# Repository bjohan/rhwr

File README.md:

# rhwr
backend and support system for rhwr from tornado aircraft. mostly a mess...

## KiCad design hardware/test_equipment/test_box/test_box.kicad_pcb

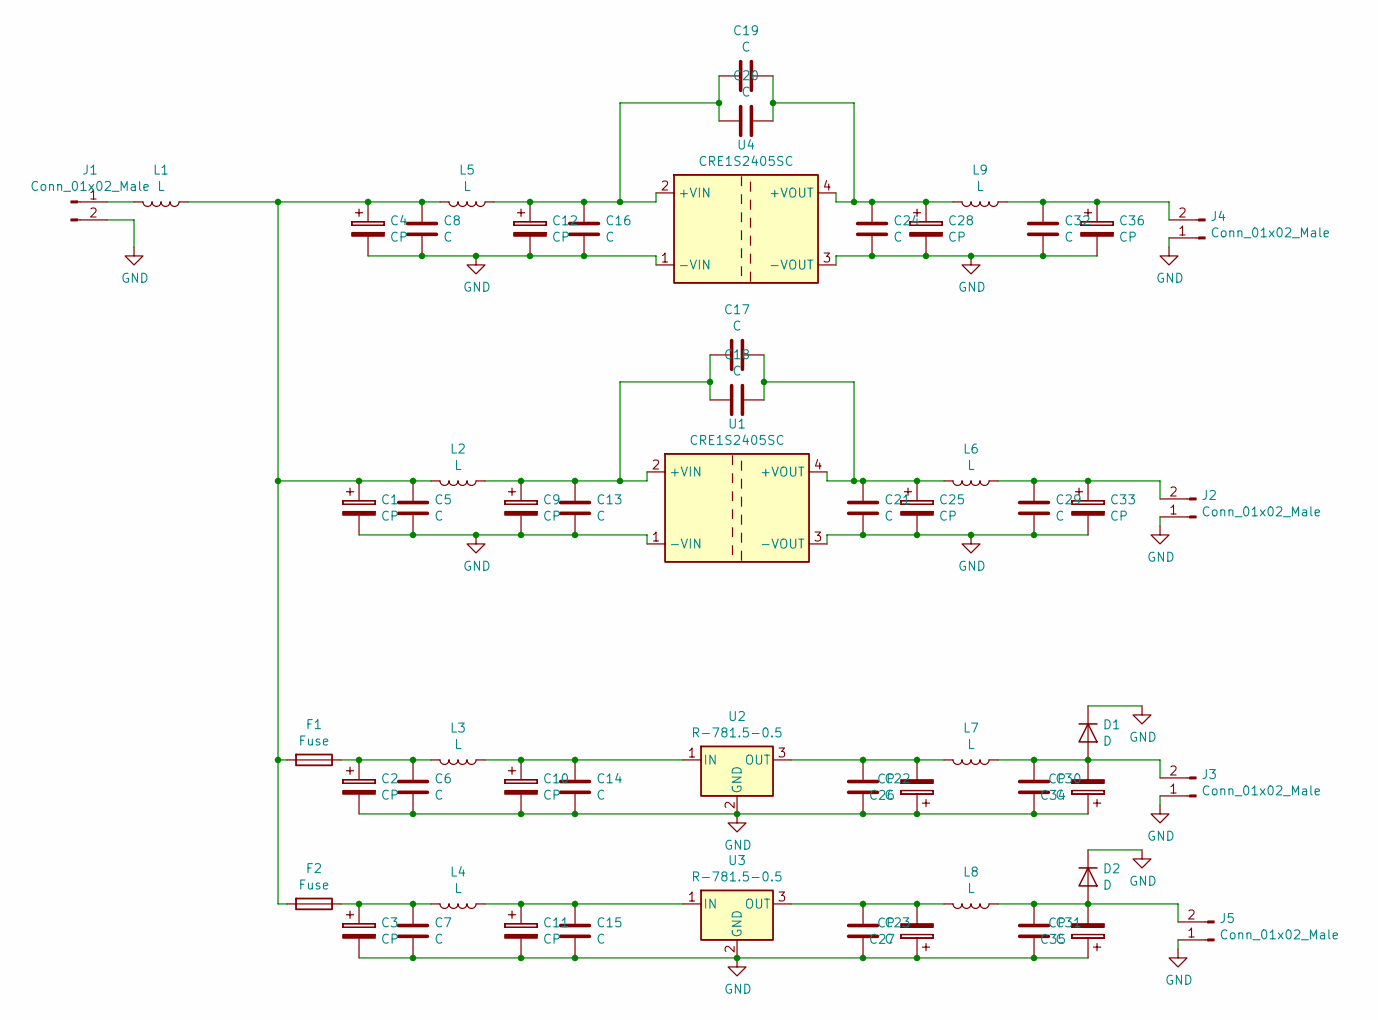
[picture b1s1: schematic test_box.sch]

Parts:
C1, C2, C3, C4, C9, C10, C11, C12, C25, C26, C27, C28, C33, C34, C35, C36: CP; CP_Elec_10x10.5
C5, C6, C7, C8, C13, C14, C15, C16, C17, C18, C19, C20, C21, C22, C23, C24, C29, C30, C31, C32: C; C_1206
D1, D2: D; D_2010
F1, F2: Fuse; R_1206
J1, J2, J3, J4, J5: Conn_01x02_Male; Molex_KK-6410-02_02x2.54mm_Straight
L1, L2, L3, L4, L5, L6, L7, L8, L9: L; Neosid_Inductor_SM-NE127
U1: CRE1S2405SC; 2149f
U2, U3: R-781.5-0.5; 0663ac
U4: CRE1S2405SC; cn6009psu

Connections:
GND: C1.2, C2.2, C3.2, C4.2, C5.2, C6.2, C7.2, C8.2, C9.2, C10.2, C11.2, C12.2, C13.2, C14.2, C15.2, C16.2, C21.2, C22.2, C23.2, C24.2, C25.2, C26.1, C27.1, C28.2, C29.2, C30.2, C31.2, C32.2, C33.2, C34.1, C35.1, C36.2, D1.1 (K), D2.1 (K), J1.2, J2.1, J3.1, J4.1, J5.1, U1.1 (-VIN), U1.3 (-VOUT), U2.2 (GND), U3.2 (GND), U4.1 (-VIN), U4.3 (-VOUT)
unnamed: C1.1, C4.1, C5.1, C8.1, F1.2, F2.2, L1.1, L2.2, L5.2
unnamed: C2.1, C6.1, F1.1, L3.2
unnamed: C3.1, C7.1, F2.1, L4.2
unnamed: C10.1, C14.1, L3.1, U2.1 (IN)
unnamed: C11.1, C15.1, L4.1, U3.1 (IN)
unnamed: C12.1, C16.1, C19.2, C20.2, L5.1, U4.2 (+VIN)
unnamed: C9.1, C13.1, C17.2, C18.2, L2.1, U1.2 (+VIN)
unnamed: C17.1, C18.1, C21.1, C25.1, L6.2, U1.4 (+VOUT)
unnamed: C19.1, C20.1, C24.1, C28.1, L9.2, U4.4 (+VOUT)
unnamed: C22.1, C26.2, L7.2, U2.3 (OUT)
unnamed: C23.1, C27.2, L8.2, U3.3 (OUT)
unnamed: C29.1, C33.1, J2.2, L6.1
unnamed: C30.1, C34.2, D1.2 (A), J3.2, L7.1
unnamed: C31.1, C35.2, D2.2 (A), J5.2, L8.1
unnamed: C32.1, C36.1, J4.2, L9.1
unnamed: J1.1, L1.2

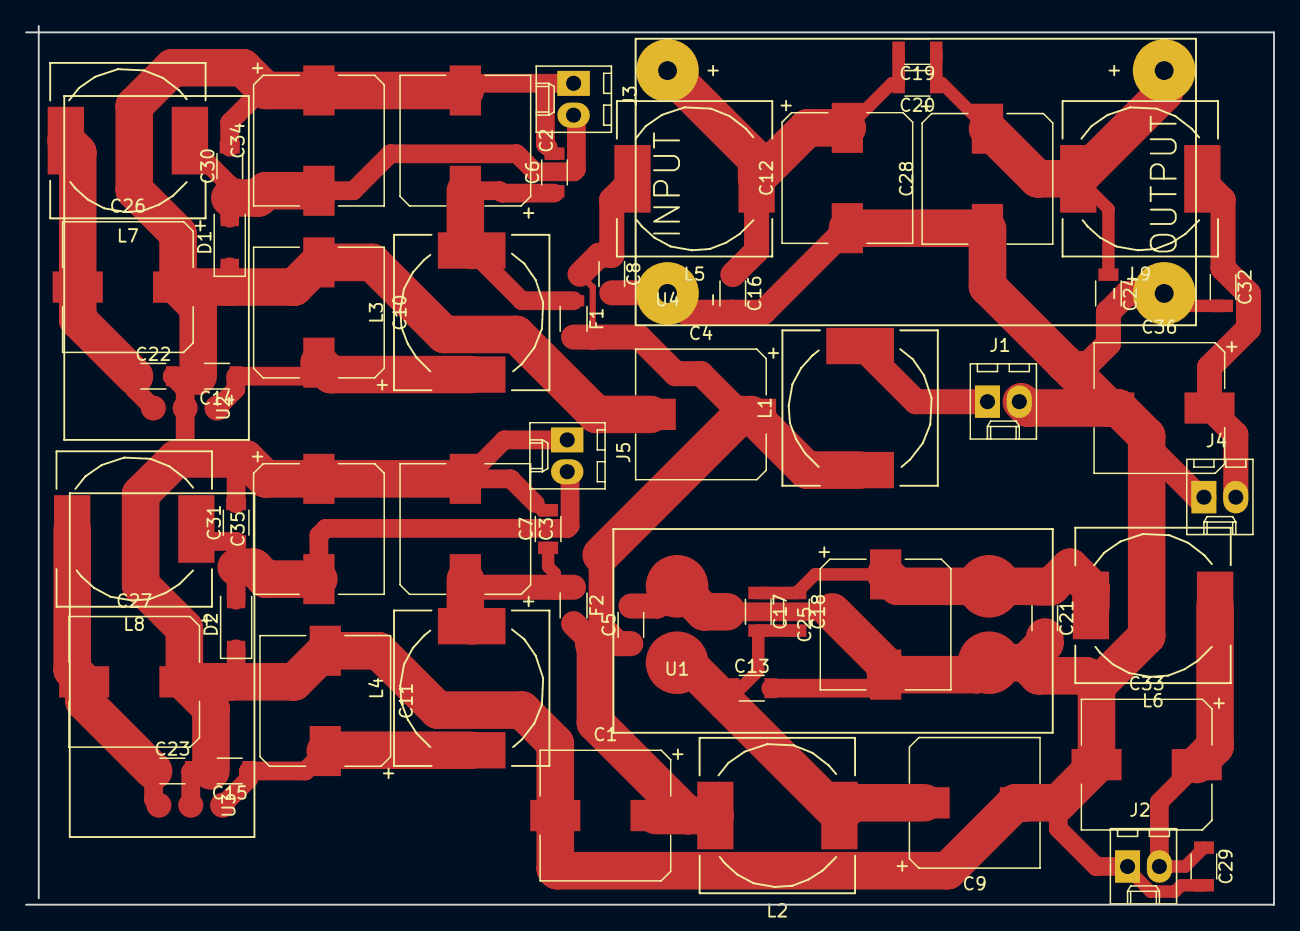
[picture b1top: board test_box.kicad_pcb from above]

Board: 2 copper layers, 99.6 x 70.1 mm, 58 parts (0 on the bottom side), 17 nets.

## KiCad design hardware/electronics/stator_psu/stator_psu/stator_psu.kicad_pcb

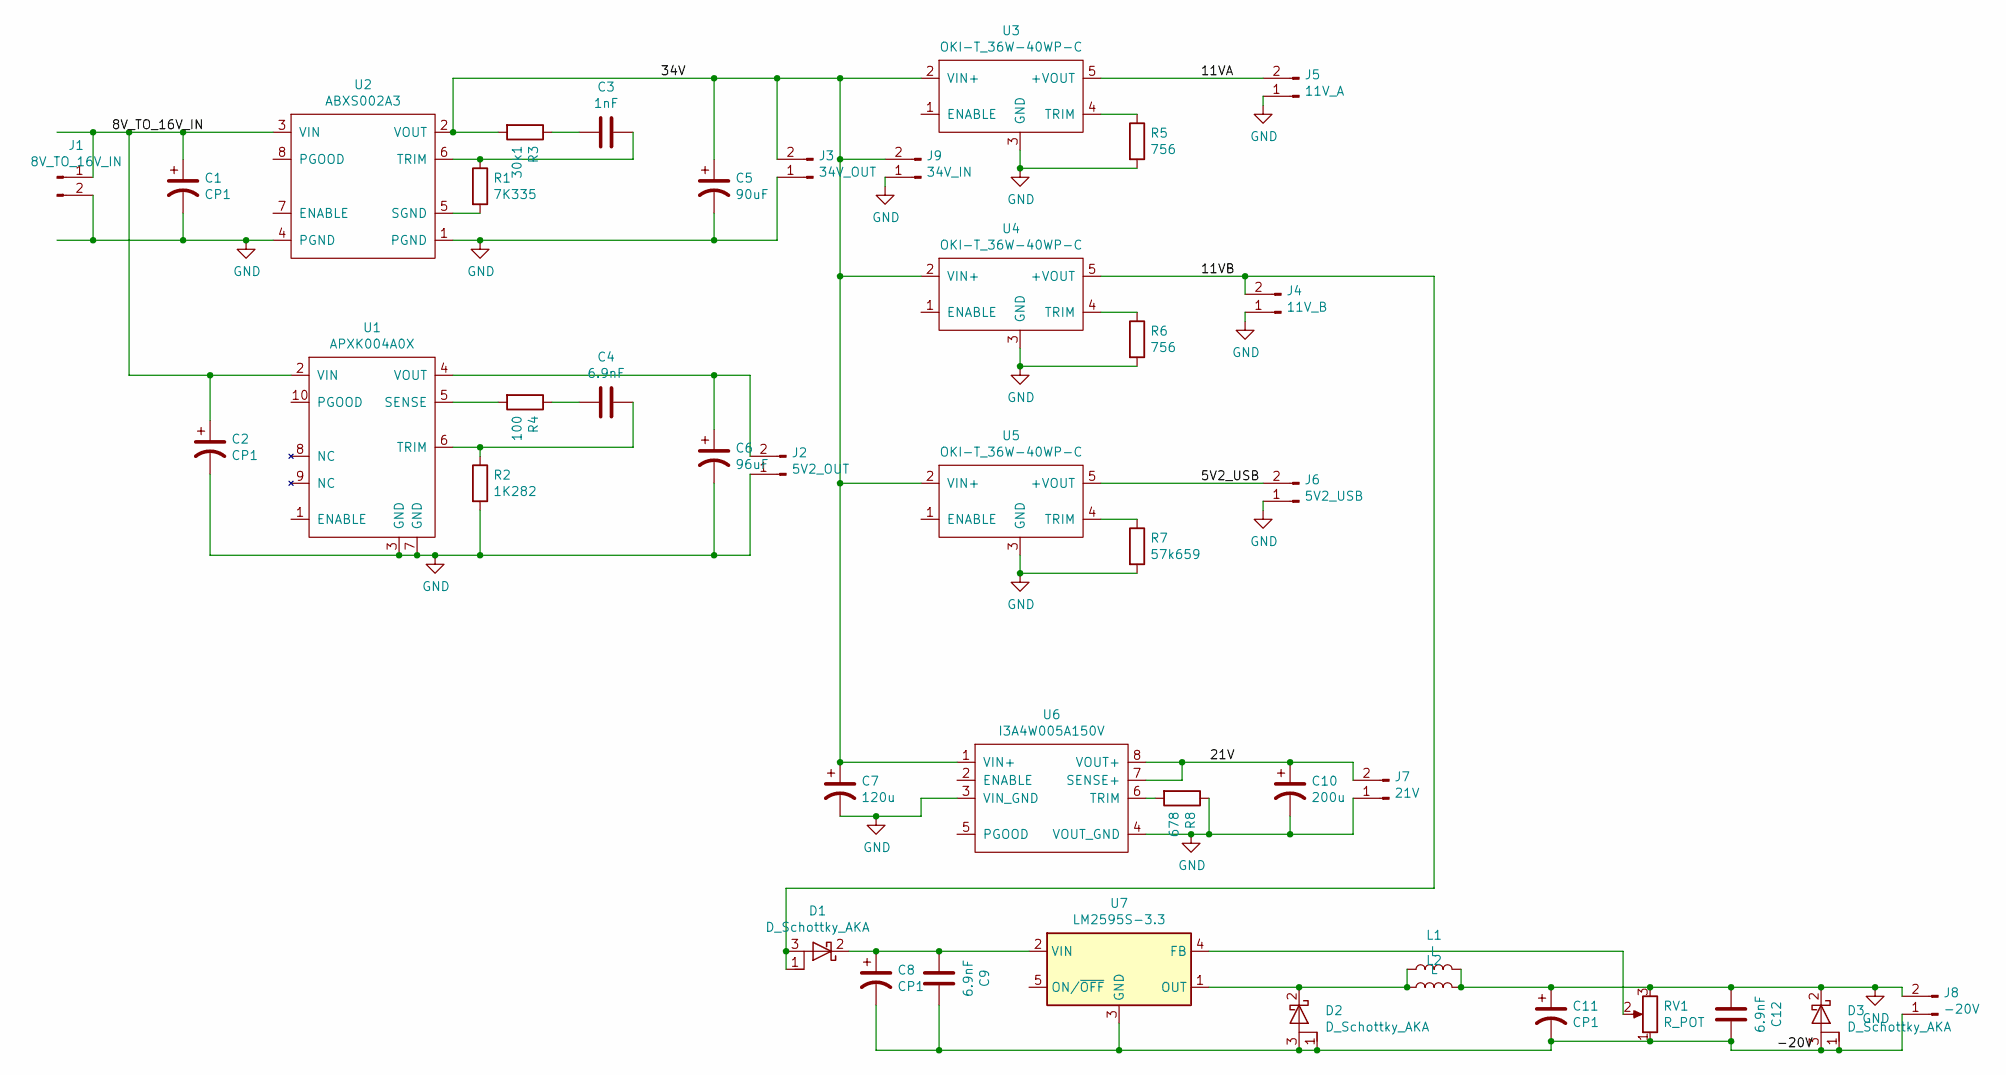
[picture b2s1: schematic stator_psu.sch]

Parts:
C1, C2, C8, C11: CP1; CP_Elec_10x10.5
C3: 1nF; C_1206
C4, C9, C12: 6.9nF; C_1206
C5: 90uF; CP_Elec_10x10.5
C6: 96uF; CP_Elec_10x10.5
C7: 120u; CP_Elec_10x10.5
C10: 200u; CP_Elec_10x10.5
D1, D2, D3: D_Schottky_AKA; TO-220
J1: 8V_TO_16V_IN; PhoenixContact_MSTBA-G_02x5.08mm_Angled
J2: 5V2_OUT; PhoenixContact_MSTBA-G_02x5.08mm_Angled
J3: 34V_OUT; PhoenixContact_MSTBA-G_02x5.08mm_Angled
J4: 11V_B; Molex_SPOX-5267_22-03-5025_02x2.54mm_Straight
J5: 11V_A; Molex_SPOX-5267_22-03-5025_02x2.54mm_Straight
J6: 5V2_USB; PhoenixContact_MSTBA-G_02x5.08mm_Angled
J7: 21V; Molex_SPOX-5267_22-03-5025_02x2.54mm_Straight
J8: -20V; Molex_SPOX-5267_22-03-5025_02x2.54mm_Straight
J9: 34V_IN; PhoenixContact_MSTBA-G_02x5.08mm_Angled
L1, L2: L; Neosid_Inductor_Ms95
R1: 7K335; R_1206
R2: 1K282; R_1206
R3: 30k1; R_1206
R4: 100; R_1206
R5, R6: 756; R_1206
R7: 57k659; R_1206
R8: 678; R_1206
RV1: R_POT; POT_SMD
U1: APXK004A0X
U2: ABXS002A3
U3, U4, U5: OKI-T_36W-40WP-C; OKI-T_36W-w40
U6: I3A4W005A150V; I3A4W005A150
U7: LM2595S-3.3; TO-263-5_TabPin3

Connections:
/5V2_USB: J6.2, U5.5 (+VOUT)
/8V_TO_16V_IN: C1.1, C2.1, J1.1, U1.2 (VIN), U2.3 (VIN)
/11VA: J5.2, U3.5 (+VOUT)
/11VB: D1.1 (A), D1.3 (A), J4.2, U4.5 (+VOUT)
/21V: C10.1, J7.2, U6.7 (SENSE+), U6.8 (VOUT+)
/34V: C5.1, C7.1, J3.2, J9.2, R3.2, U2.2 (VOUT), U3.2 (VIN+), U4.2 (VIN+), U5.2 (VIN+), U6.1 (VIN+)
/-20V: C8.2, C9.1, C11.2, C12.1, D2.1 (A), D2.3 (A), D3.1 (A), D3.3 (A), J8.1, RV1.1, U7.3 (GND)
GND: C1.2, C2.2, C5.2, C6.2, C7.2, C10.2, C11.1, C12.2, D3.2 (K), J1.2, J2.1, J3.1, J4.1, J5.1, J6.1, J7.1, J8.2, J9.1, L1.2, L2.2, R2.2, R5.2, R6.2, R7.2, R8.1, RV1.3, U1.3 (GND), U1.7 (GND), U2.1 (PGND), U2.4 (PGND), U3.3 (GND), U4.3 (GND), U5.3 (GND), U6.3 (VIN_GND), U6.4 (VOUT_GND)
unnamed: C3.1, R1.1, U2.6 (TRIM)
unnamed: C3.2, R3.1
unnamed: C4.1, R2.1, U1.6 (TRIM)
unnamed: C4.2, R4.1
unnamed: C6.1, J2.2, U1.4 (VOUT)
unnamed: C8.1, C9.2, D1.2 (K), U7.2 (VIN)
unnamed: D2.2 (K), L1.1, L2.1, U7.1 (OUT)
unnamed: R1.2, U2.5 (SGND)
unnamed: R4.2, U1.5 (SENSE)
unnamed: R5.1, U3.4 (TRIM)
unnamed: R6.1, U4.4 (TRIM)
unnamed: R7.1, U5.4 (TRIM)
unnamed: R8.2, U6.6 (TRIM)
unnamed: RV1.2, U7.4 (FB)

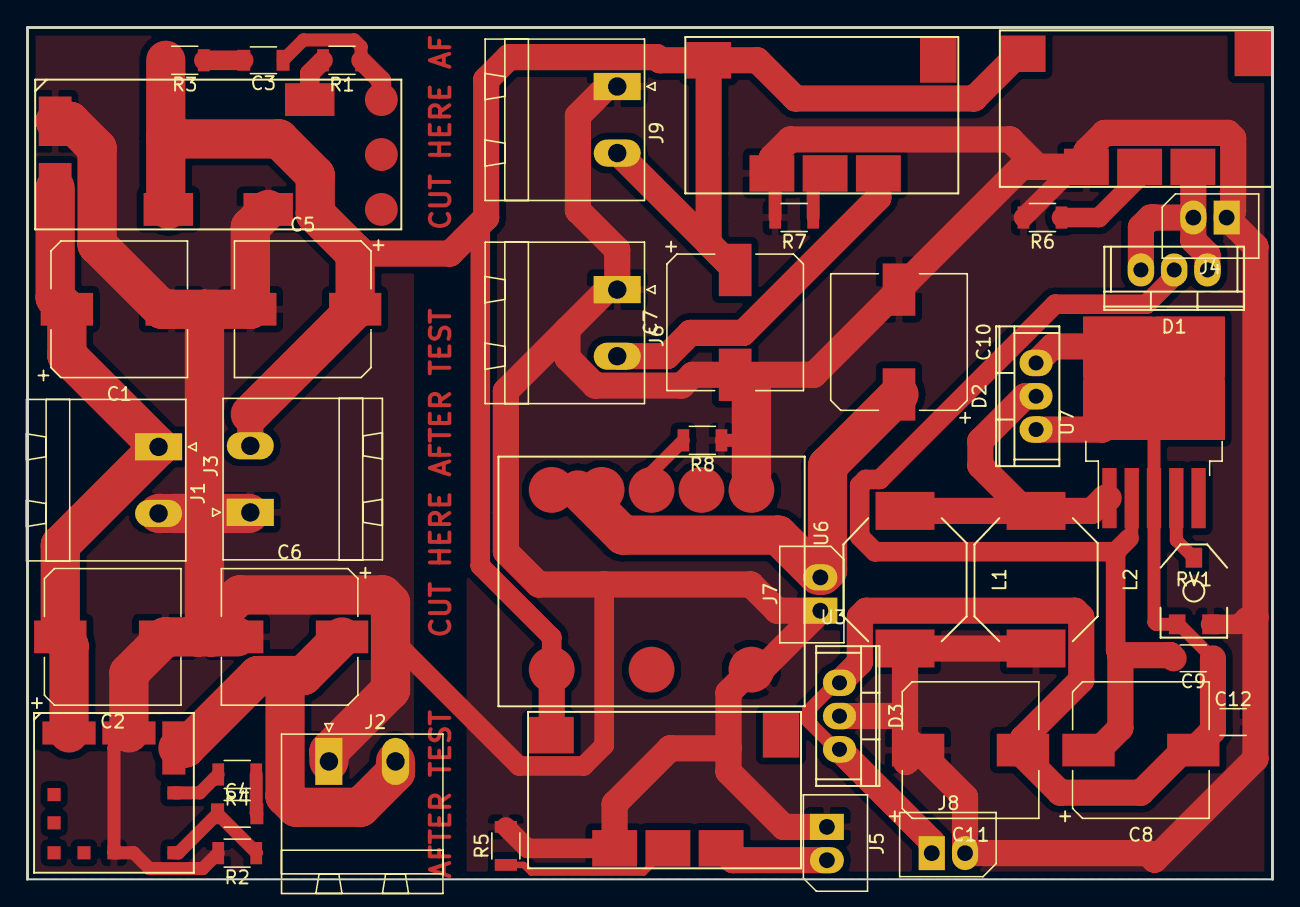
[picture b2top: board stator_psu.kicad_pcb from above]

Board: 2 copper layers, 95.0 x 65.0 mm, 42 parts (0 on the bottom side), 22 nets.

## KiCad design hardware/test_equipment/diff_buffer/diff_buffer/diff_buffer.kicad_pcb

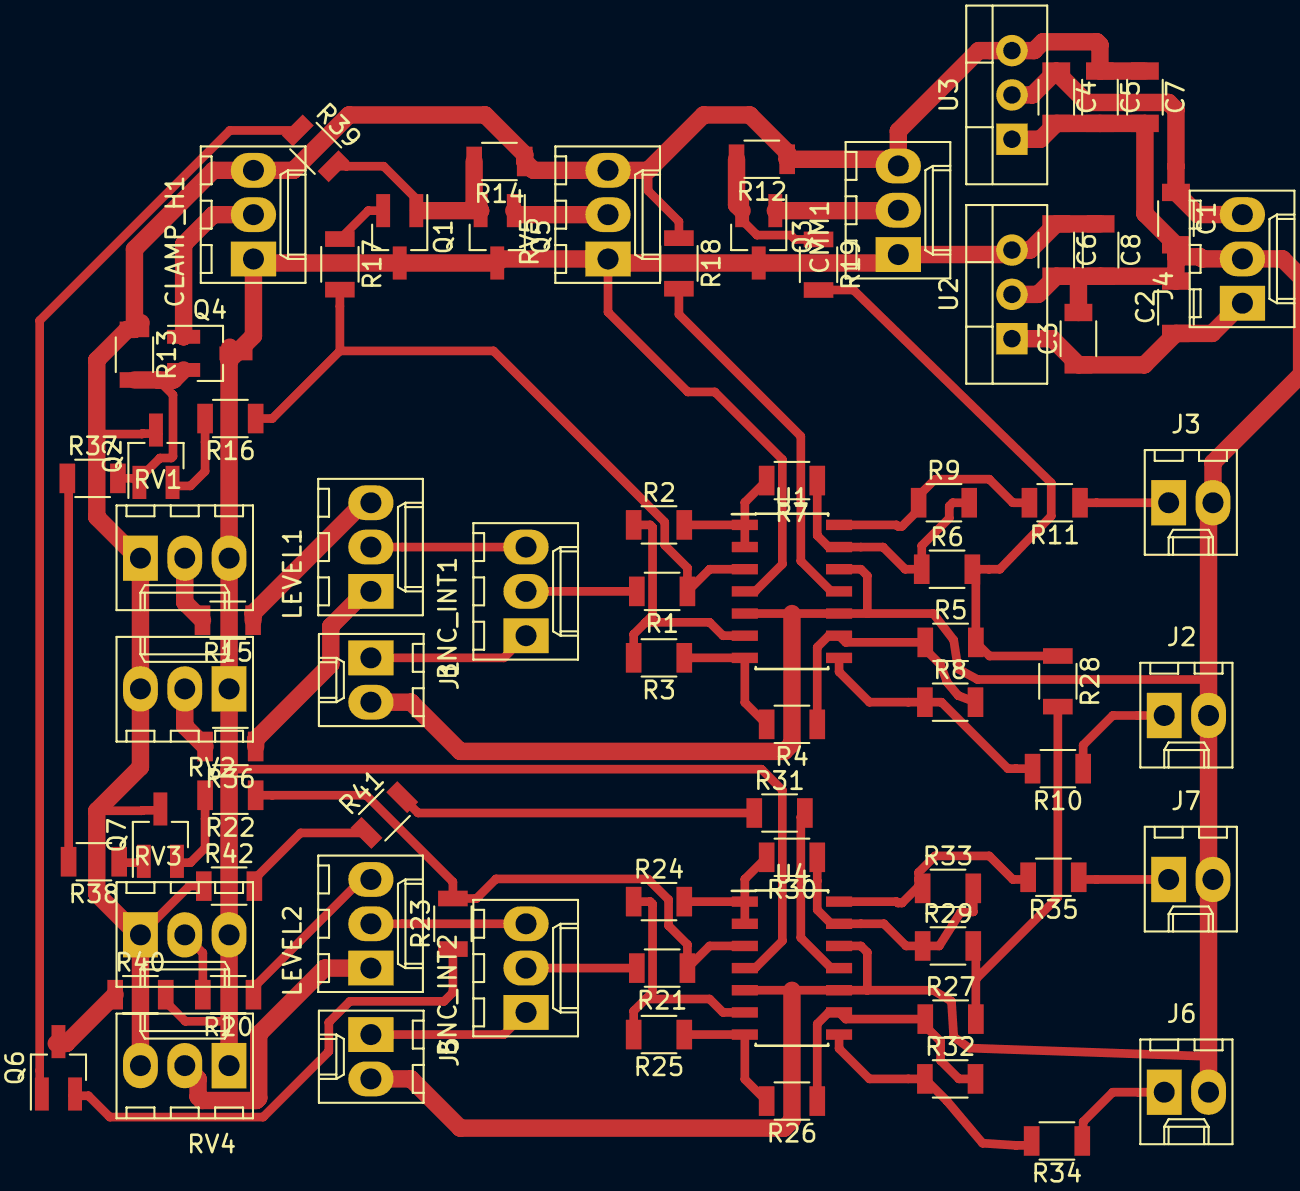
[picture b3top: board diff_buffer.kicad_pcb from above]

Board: 2 copper layers, 79 parts (0 on the bottom side), 58 nets.

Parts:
BNC_INT1, BNC_INT2: SW_SPDT; Molex_KK-6410-03_03x2.54mm_Straight
C1, C2, C3, C4, C5, C6, C7, C8: C; C_1206
CLAMP_H1: R_POT; Molex_KK-6410-03_03x2.54mm_Straight
CMM1: R_POT; Molex_KK-6410-03_03x2.54mm_Straight
J1, J5: INPUT; Molex_KK-6410-02_02x2.54mm_Straight
J2, J6: ~OUT; Molex_KK-6410-02_02x2.54mm_Straight
J3, J7: OUT; Molex_KK-6410-02_02x2.54mm_Straight
J4: Conn_01x03_Male; Molex_KK-6410-03_03x2.54mm_Straight
LEVEL1, LEVEL2: SW_SPDT; Molex_KK-6410-03_03x2.54mm_Straight
Q1, Q6: Q_NPN_BEC; SOT-23_Handsoldering
Q2, Q3, Q4, Q5, Q7: Q_PNP_BEC; SOT-23_Handsoldering
R1, R2, R3, R4, R5, R6, R7, R8, R9, R21, R24, R25, R26, R27, R29, R30, R32, R33: 100K; R_1206
R10, R11, R34, R35: 10K; R_1206
R12, R13, R14, R18, R39: R; R_1206
R15, R19, R20, R28, R31, R36, R37, R38, R40, R41, R42: 0; R_1206
R16, R17, R22, R23: 2K; R_1206
RV1, RV2, RV3, RV4: R_POT; Molex_KK-6410-03_03x2.54mm_Straight
RV5: CLAMP_L; Molex_KK-6410-03_03x2.54mm_Straight
U1, U4: LM324; SOIC-14_3.9x8.7mm_Pitch1.27mm
U2: L7812; TO-220-3_Vertical
U3: L7912; TO-220-3_Vertical

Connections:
+15V: C6.1, C8.1, CLAMP_H1.1, CMM1.1, Q1.3, Q3.3, Q4.3, Q5.3, R40.2, RV1.3, RV2.1, RV3.3, RV4.1, RV5.1, U1.4, U2.3, U4.4
-15V: C5.1, C7.1, CLAMP_H1.3, CMM1.3, Q2.3, Q7.3, R12.1, R13.1, R14.1, R18.1, R42.1, RV1.1, RV2.3, RV3.1, RV4.3, RV5.3, U3.3
/neg_clamp_voltage: Q1.1, Q5.2, R14.2, R39.2
/offset_voltage: Q3.2, R12.2, R19.1
/offset_voltage2: R5.2, R6.2, R19.2, R28.1
/pos_clamp_voltage: Q2.1, Q4.2, R13.2, R37.2
GND: C1.2, C2.2, C3.2, C4.2, C5.2, C6.2, C7.2, C8.2, J1.2, J2.2, J3.2, J4.2, J5.2, J6.2, J7.2, U1.5, U1.10, U1.12, U2.2, U3.1, U4.5, U4.10, U4.12
unnamed: BNC_INT1.1, J1.1
unnamed: BNC_INT1.2, R1.2
unnamed: BNC_INT1.3, LEVEL1.2
unnamed: BNC_INT2.1, J5.1
unnamed: BNC_INT2.2, R21.2
unnamed: BNC_INT2.3, LEVEL2.2
unnamed: C1.1, C4.1, J4.3, U3.2
unnamed: C2.1, C3.1, J4.1, U2.1
unnamed: CLAMP_H1.2, Q4.1
unnamed: CMM1.2, Q3.1
unnamed: J2.1, R10.1
unnamed: J3.1, R11.1
unnamed: J6.1, R34.1
unnamed: J7.1, R35.1
unnamed: LEVEL1.1, R36.1
unnamed: LEVEL1.3, R15.1
unnamed: LEVEL2.1, RV4.2
unnamed: LEVEL2.3, R20.1
unnamed: Q1.2, R17.1
unnamed: Q2.2, R16.2
unnamed: Q5.1, RV5.2
unnamed: Q6.1, R39.1
unnamed: Q6.2, R23.1
unnamed: Q6.3, R40.1
unnamed: Q7.1, R38.1
unnamed: Q7.2, R22.2
unnamed: R1.1, R16.1, R17.2, U1.3
unnamed: R2.1, R3.2, U1.6
unnamed: R2.2, R7.2, U1.1, U1.2
unnamed: R3.1, R4.2, U1.7
unnamed: R4.1, R5.1, R8.2, U1.9
unnamed: R6.1, R7.1, R9.2, U1.13
unnamed: R8.1, R10.2, U1.8
unnamed: R9.1, R11.2, U1.14
unnamed: R15.2, RV1.2
unnamed: R18.2, U1.11
unnamed: R20.2, RV3.2
unnamed: R21.1, R22.1, R23.2, U4.3
unnamed: R24.1, R25.2, U4.6
unnamed: R24.2, R30.2, U4.1, U4.2
unnamed: R25.1, R26.2, U4.7
unnamed: R26.1, R27.1, R32.2, U4.9
unnamed: R27.2, R28.2, R29.2
unnamed: R29.1, R30.1, R33.2, U4.13
unnamed: R31.1, R41.2
unnamed: R31.2, U4.11
unnamed: R32.1, R34.2, U4.8
unnamed: R33.1, R35.2, U4.14
unnamed: R36.2, RV2.2
unnamed: R37.1, R38.2
unnamed: R41.1, R42.2

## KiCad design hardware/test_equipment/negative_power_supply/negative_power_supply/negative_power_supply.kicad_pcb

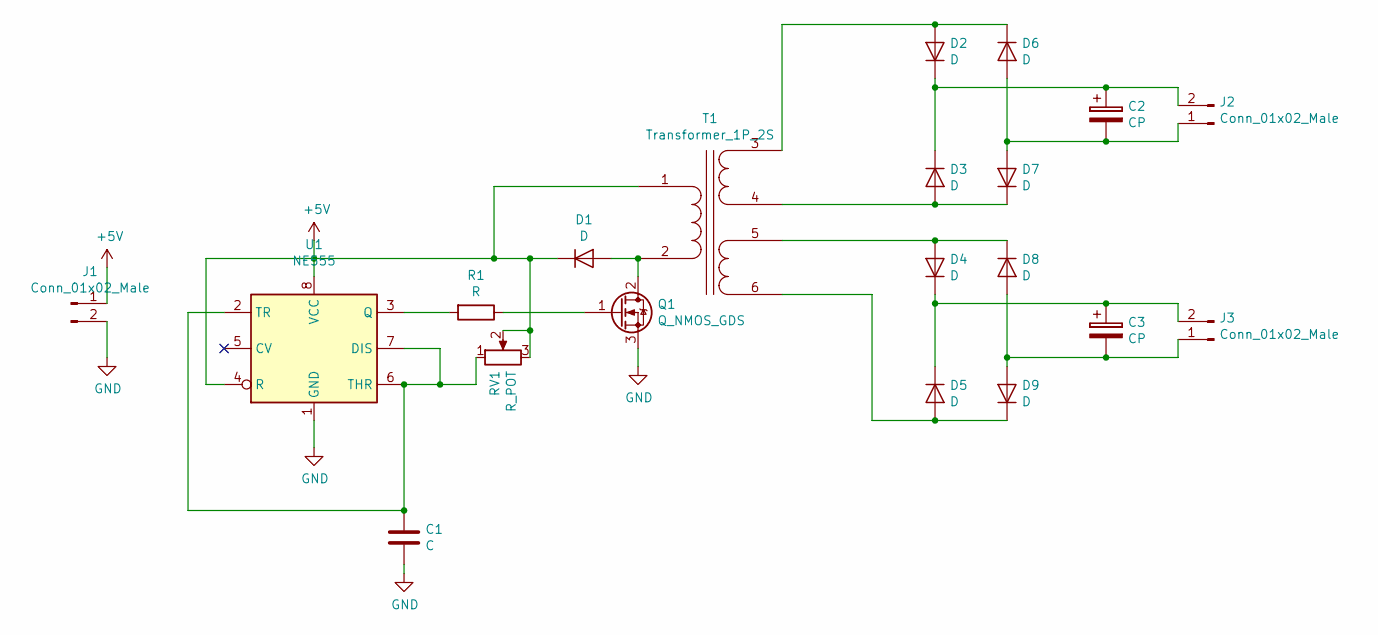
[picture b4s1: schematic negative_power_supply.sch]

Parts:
C1: C; C_1206
C2, C3: CP; CP_Elec_10x10.5
D1, D2, D3, D4, D5, D6, D7, D8, D9: D; D_SMA_Handsoldering
J1, J2, J3: Conn_01x02_Male; Molex_KK-6410-02_02x2.54mm_Straight
Q1: Q_NMOS_GDS; TO-220
R1: R; R_1206
RV1: R_POT; Potentiometer_Trimmer_ACP_CA6VSMD_Horizontal
T1: Transformer_1P_2S; Molex_KK-6410-06_06x2.54mm_Straight
U1: NE555; DIP-8_W7.62mm_LongPads

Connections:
+5V: D1.1 (K), J1.1, RV1.2, RV1.3, T1.1 (AA), U1.4 (R), U1.8 (VCC)
GND: C1.2, J1.2, Q1.3 (S), U1.1 (GND)
unnamed: C1.1, RV1.1, U1.2 (TR), U1.6 (THR), U1.7 (DIS)
unnamed: C2.1, D2.1 (K), D3.1 (K), J2.2
unnamed: C2.2, D6.2 (A), D7.2 (A), J2.1
unnamed: C3.1, D4.1 (K), D5.1 (K), J3.2
unnamed: C3.2, D8.2 (A), D9.2 (A), J3.1
unnamed: D1.2 (A), Q1.2 (D), T1.2 (AB)
unnamed: D2.2 (A), D6.1 (K), T1.3 (SA)
unnamed: D3.2 (A), D7.1 (K), T1.4 (SB)
unnamed: D4.2 (A), D8.1 (K), T1.5 (SC)
unnamed: D5.2 (A), D9.1 (K), T1.6 (SD)
unnamed: Q1.1 (G), R1.1
unnamed: R1.2, U1.3 (Q)

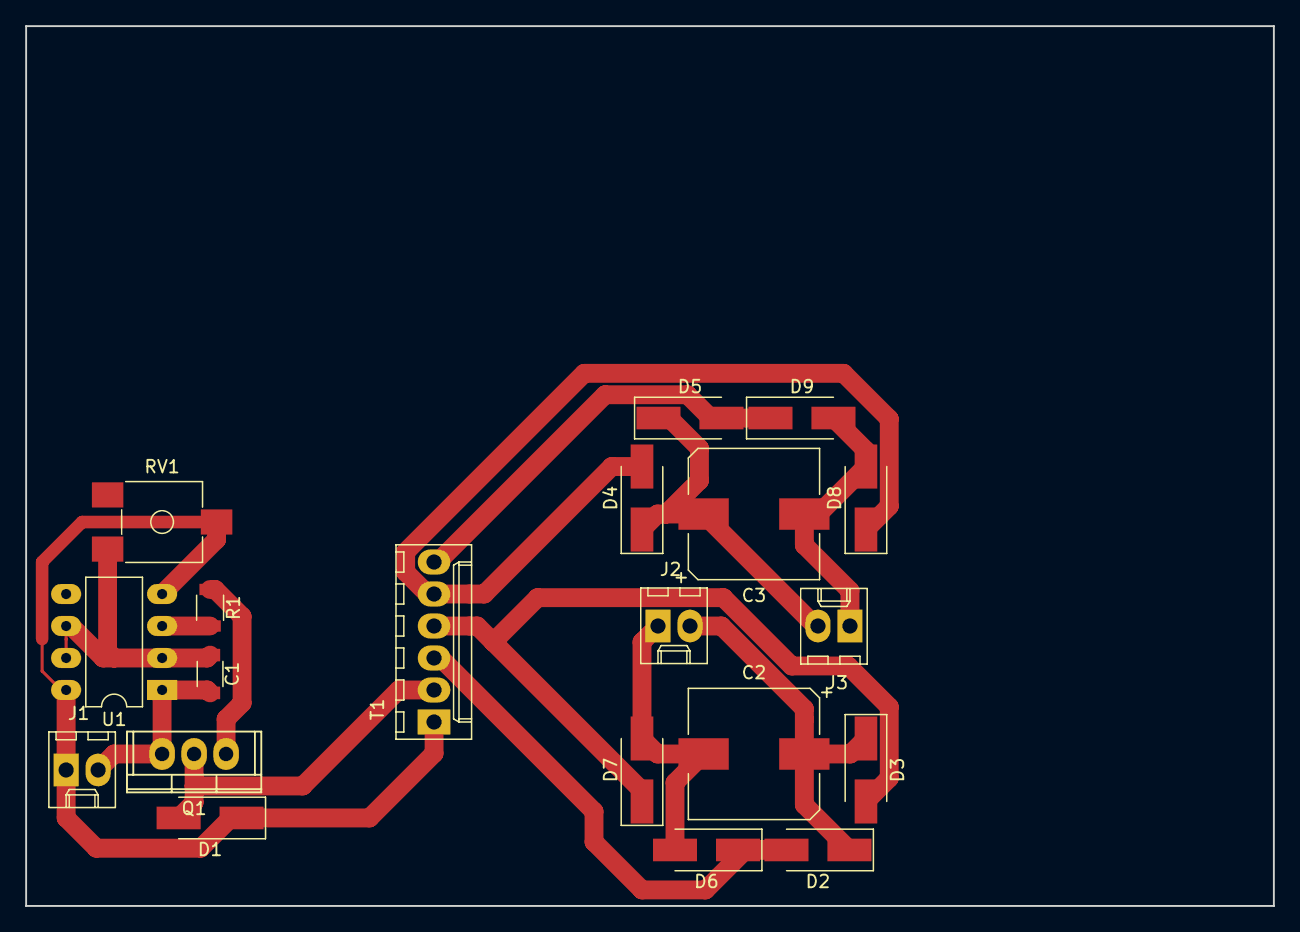
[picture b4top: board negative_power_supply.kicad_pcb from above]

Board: 2 copper layers, 99.1 x 69.9 mm, 20 parts (0 on the bottom side), 14 nets.

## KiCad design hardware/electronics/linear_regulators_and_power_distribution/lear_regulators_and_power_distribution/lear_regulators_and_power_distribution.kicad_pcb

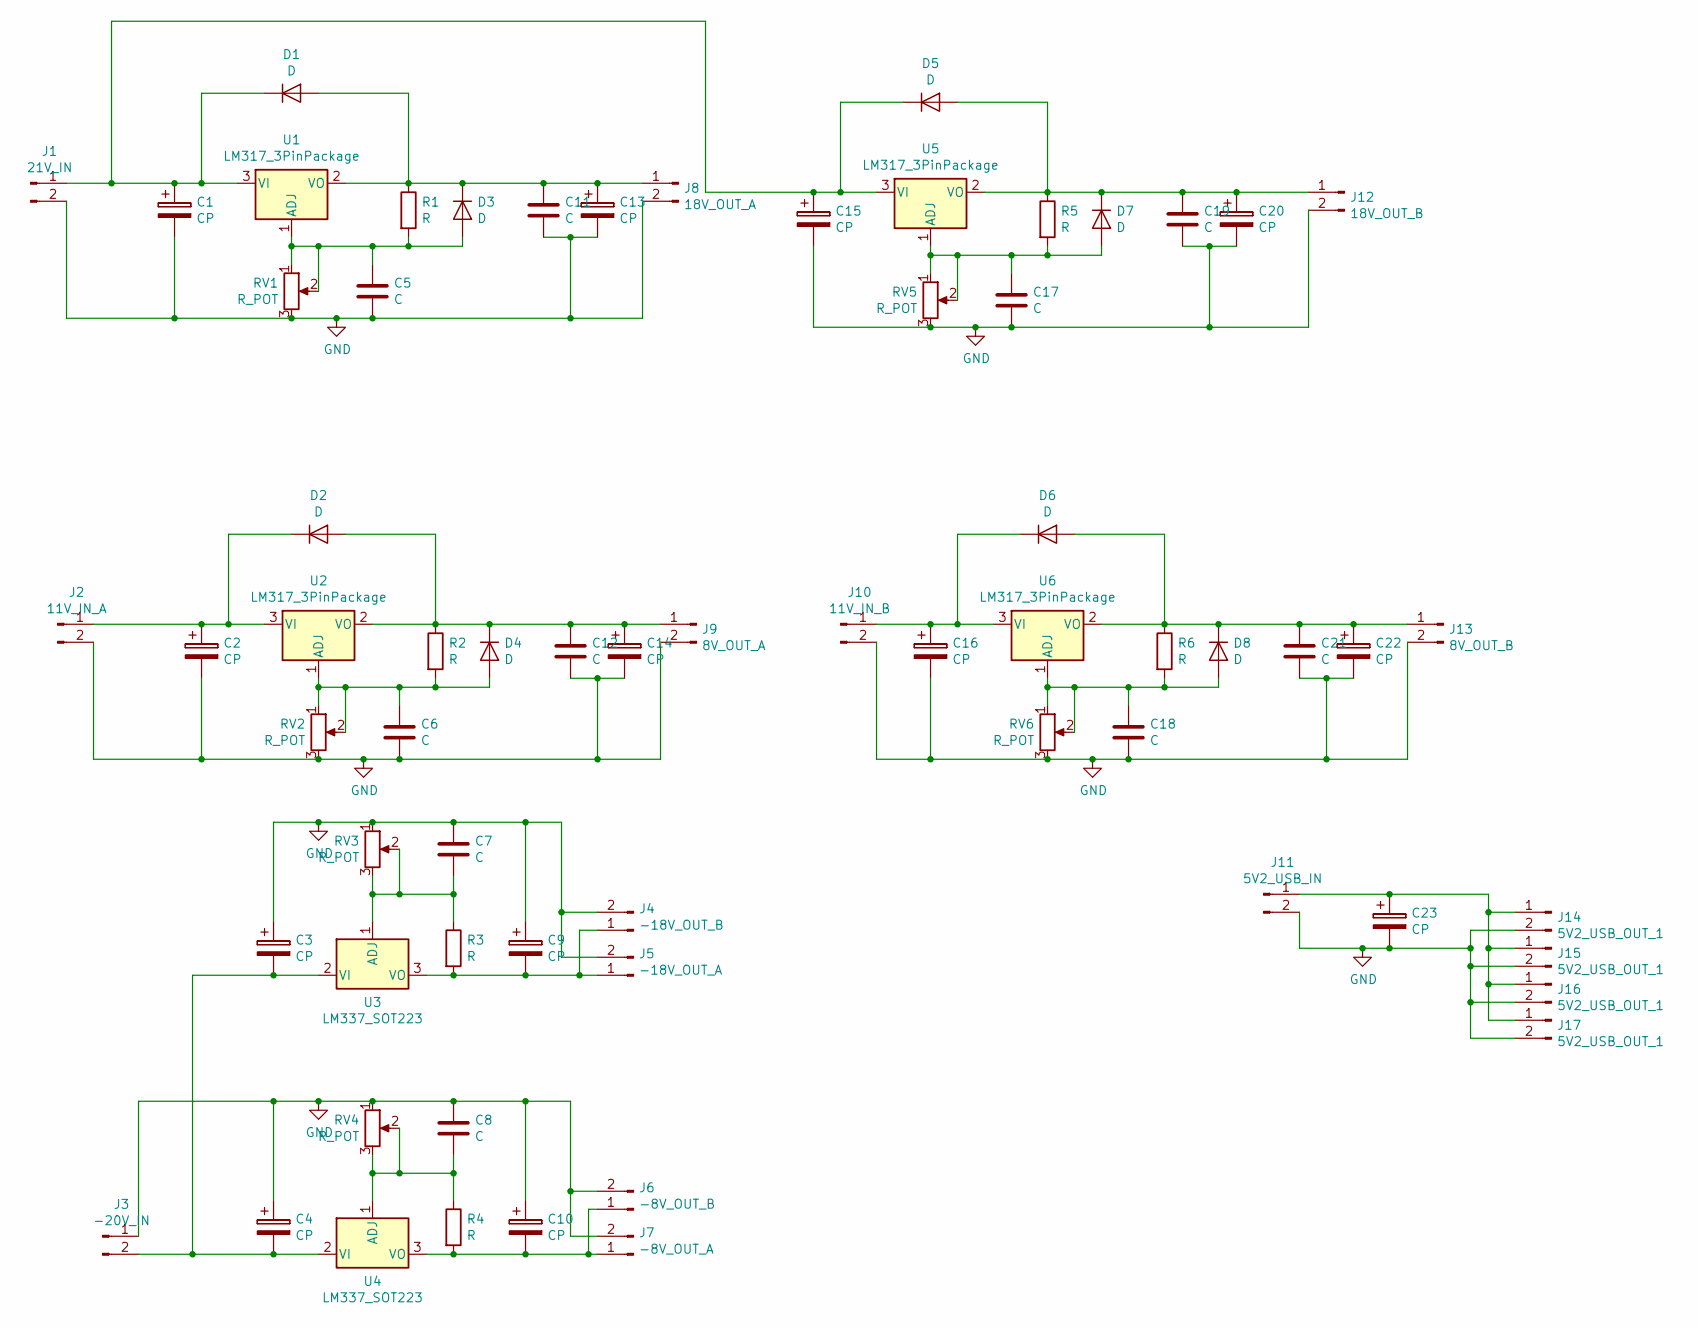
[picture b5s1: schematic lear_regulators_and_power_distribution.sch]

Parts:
C1, C2, C3, C4, C9, C10, C13, C14, C15, C16, C20, C22, C23: CP; CP_Elec_10x10.5
C5, C6, C7, C8, C11, C12, C17, C18, C19, C21: C; C_1206
D1, D2, D3, D4, D5, D6, D7, D8: D; D_2114
J1: 21V_IN; Molex_SPOX-5267_22-03-5025_02x2.54mm_Straight
J2: 11V_IN_A; Molex_SPOX-5267_22-03-5025_02x2.54mm_Straight
J3: -20V_IN; Molex_SPOX-5267_22-03-5025_02x2.54mm_Straight
J4: -18V_OUT_B; Molex_SPOX-5267_22-03-5025_02x2.54mm_Straight
J5: -18V_OUT_A; Molex_SPOX-5267_22-03-5025_02x2.54mm_Straight
J6: -8V_OUT_B; Molex_SPOX-5267_22-03-5025_02x2.54mm_Straight
J7: -8V_OUT_A; Molex_SPOX-5267_22-03-5025_02x2.54mm_Straight
J8: 18V_OUT_A; Molex_SPOX-5267_22-03-5025_02x2.54mm_Straight
J9: 8V_OUT_A; Molex_SPOX-5267_22-03-5025_02x2.54mm_Straight
J10: 11V_IN_B; Molex_SPOX-5267_22-03-5025_02x2.54mm_Straight
J11: 5V2_USB_IN; Molex_SPOX-5267_22-03-5025_02x2.54mm_Straight
J12: 18V_OUT_B; Molex_SPOX-5267_22-03-5025_02x2.54mm_Straight
J13: 8V_OUT_B; Molex_SPOX-5267_22-03-5025_02x2.54mm_Straight
J14, J15, J16, J17: 5V2_USB_OUT_1; Molex_SPOX-5267_22-03-5025_02x2.54mm_Straight
R1, R2, R3, R4, R5, R6: R; R_1206
RV1, RV2, RV3, RV4, RV5, RV6: R_POT; Potentiometer_Trimmer_Vishay_TS53YL
U1, U2, U5, U6: LM317_3PinPackage; TO-220
U3, U4: LM337_SOT223; TO-220

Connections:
GND: C1.2, C2.2, C3.1, C4.1, C5.2, C6.2, C7.1, C8.1, C9.1, C10.1, C11.2, C12.2, C13.2, C14.2, C15.2, C16.2, C17.2, C18.2, C19.2, C20.2, C21.2, C22.2, C23.2, J1.2, J2.2, J3.1, J4.2, J5.2, J6.2, J7.2, J8.2, J9.2, J10.2, J11.2, J12.2, J13.2, J14.2, J15.2, J16.2, J17.2, RV1.3, RV2.3, RV3.1, RV4.1, RV5.3, RV6.3
unnamed: C1.1, C15.1, D1.1 (K), D5.1 (K), J1.1, U1.3 (VI), U5.3 (VI)
unnamed: C2.1, D2.1 (K), J2.1, U2.3 (VI)
unnamed: C3.2, C4.2, J3.2, U3.2 (VI), U4.2 (VI)
unnamed: C5.1, D3.2 (A), R1.2, RV1.1, RV1.2, U1.1 (ADJ)
unnamed: C6.1, D4.2 (A), R2.2, RV2.1, RV2.2, U2.1 (ADJ)
unnamed: C7.2, R3.1, RV3.2, RV3.3, U3.1 (ADJ)
unnamed: C8.2, R4.1, RV4.2, RV4.3, U4.1 (ADJ)
unnamed: C9.2, J4.1, J5.1, R3.2, U3.3 (VO)
unnamed: C10.2, J6.1, J7.1, R4.2, U4.3 (VO)
unnamed: C11.1, C13.1, D1.2 (A), D3.1 (K), J8.1, R1.1, U1.2 (VO)
unnamed: C12.1, C14.1, D2.2 (A), D4.1 (K), J9.1, R2.1, U2.2 (VO)
unnamed: C16.1, D6.1 (K), J10.1, U6.3 (VI)
unnamed: C17.1, D7.2 (A), R5.2, RV5.1, RV5.2, U5.1 (ADJ)
unnamed: C18.1, D8.2 (A), R6.2, RV6.1, RV6.2, U6.1 (ADJ)
unnamed: C19.1, C20.1, D5.2 (A), D7.1 (K), J12.1, R5.1, U5.2 (VO)
unnamed: C21.1, C22.1, D6.2 (A), D8.1 (K), J13.1, R6.1, U6.2 (VO)
unnamed: C23.1, J11.1, J14.1, J15.1, J16.1, J17.1

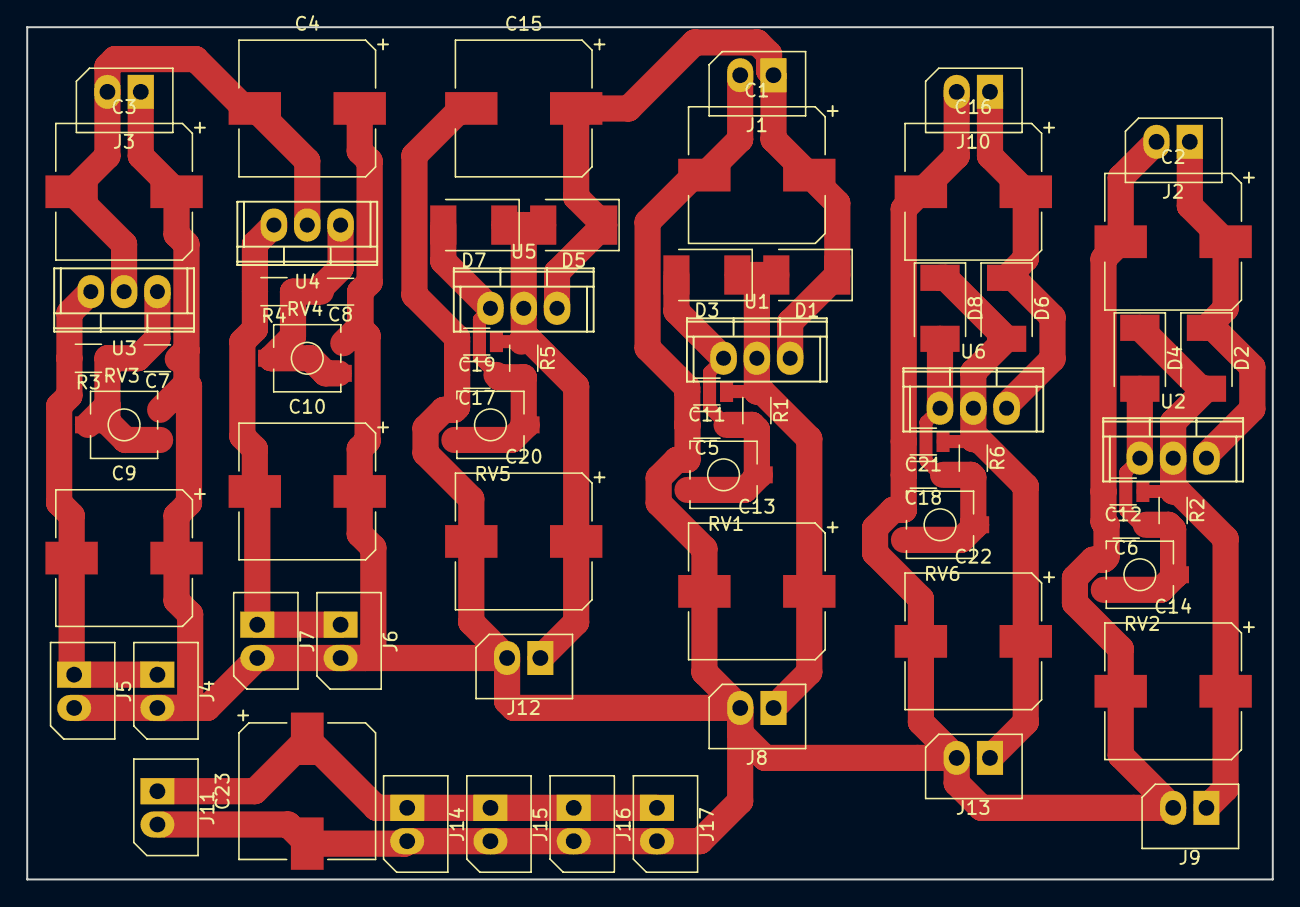
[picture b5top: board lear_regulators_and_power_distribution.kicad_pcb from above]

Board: 2 copper layers, 95.0 x 65.0 mm, 66 parts (0 on the bottom side), 18 nets.

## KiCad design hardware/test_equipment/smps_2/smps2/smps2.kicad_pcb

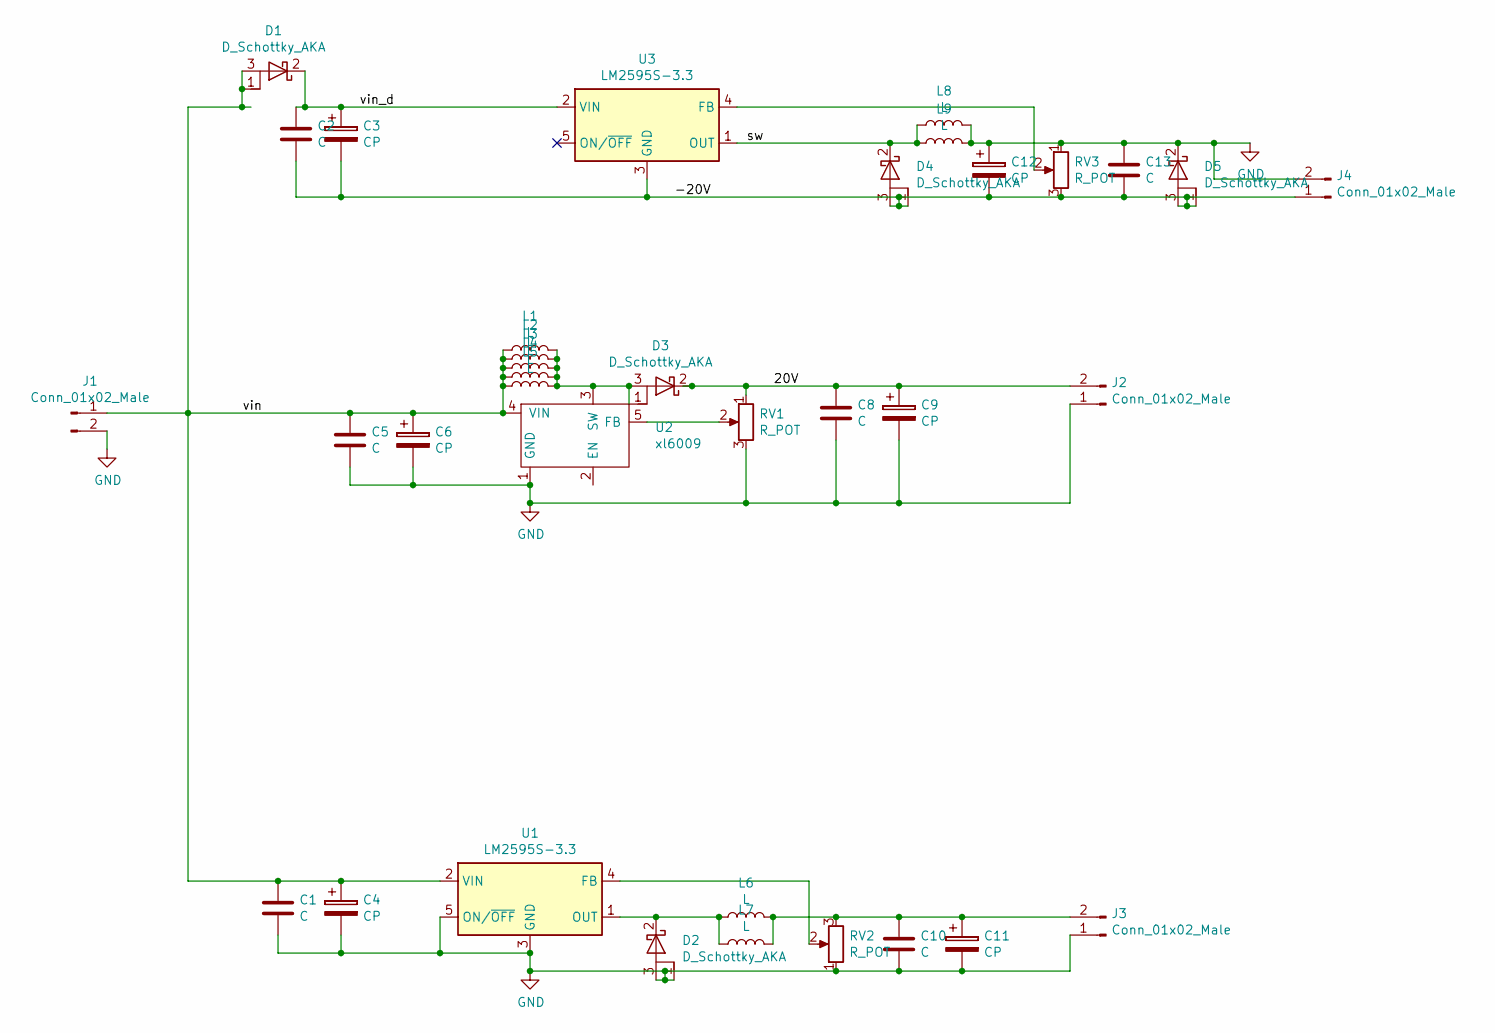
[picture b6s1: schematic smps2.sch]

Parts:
C1, C2, C5, C8, C10, C13: C; C_1206
C3, C4, C6, C9, C11, C12: CP; CP_Elec_10x10.5
D1, D2, D3, D4, D5: D_Schottky_AKA; TO-220
J1, J2, J3, J4: Conn_01x02_Male; Molex_KK-6410-02_02x2.54mm_Straight
L1, L2, L3, L4, L5, L6, L7, L8, L9: L; Neosid_Inductor_Ms95
RV1, RV2, RV3: R_POT; Potentiometer_Trimmer_Vishay_TS53YL
U1, U3: LM2595S-3.3; TO-263-5_TabPin3
U2: xl6009; TO-263-5_TabPin3

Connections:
/20V: C8.2, C9.1, D3.2 (K), J2.2, RV1.1
/-20V: C2.1, C3.2, C12.2, C13.1, D4.1 (A), D4.3 (A), D5.1 (A), D5.3 (A), J4.1, RV3.3, U3.3 (GND)
/sw: D4.2 (K), L8.1, L9.1, U3.1 (OUT)
/vin: C1.2, C4.1, C5.2, C6.1, D1.1 (A), D1.3 (A), J1.1, L1.1, L2.1, L3.1, L4.1, L5.1, U1.2 (VIN), U2.4 (VIN)
/vin_d: C2.2, C3.1, D1.2 (K), U3.2 (VIN)
GND: C1.1, C4.2, C5.1, C6.2, C8.1, C9.2, C10.1, C11.2, C12.1, C13.2, D2.1 (A), D2.3 (A), D5.2 (K), J1.2, J2.1, J3.1, J4.2, L8.2, L9.2, RV1.3, RV2.1, RV3.1, U1.3 (GND), U1.5 (ON/~OFF), U2.1 (GND)
unnamed: C10.2, C11.1, J3.2, L6.2, L7.2, RV2.3
unnamed: D2.2 (K), L6.1, L7.1, U1.1 (OUT)
unnamed: D3.1 (A), D3.3 (A), L1.2, L2.2, L3.2, L4.2, L5.2, U2.3 (SW)
unnamed: RV1.2, U2.5 (FB)
unnamed: RV2.2, U1.4 (FB)
unnamed: RV3.2, U3.4 (FB)
